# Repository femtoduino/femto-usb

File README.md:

femto-usb
=========

FemtoUSB - Atmel ARM Cortex M0+ (SAMD21), 256KB @ 48MHz, 3V3

This micro controller is designed as a basic starting point for those interested in ARM designs (especially if you are transitioning from 8-bit AVR chips).

We use Atmel's ARM Cortex M0+ offering, the ATSAMD21E18A. The schematic follows the suggested design found in the SAM D21 data sheet.

## Arduino Setup (TLDR)

Arduino compatible when using FemtoUSB (ARM) r1.0.1, with RGB LED.

Just add us to your Arduino IDE. See README https://github.com/femtoio/ArduinoCore-atsamd21e18a/tree/atsamd21e18a_variant

## Why Atmel?
Atmel has some of the best support for the open-source hardware community. They offer proper documentation, excellent chip performance, and a great foundation via the Atmel Software Framework.
Did we mention how easy it is to get started with ARM using ATMEL?

## Key similarities, and differences between 8-bit AVR chips, and newer ARM chips

So, you've been working with Arduino boards for a while now, but want to get into ARM chips right? How difficult can it be?

As it turns out, it's much less so today than it was a short time ago. Thankfully, most micro controllers have a similar set of requirements:

1. Add in some snubbing caps, as per the chip's data sheet.
2. Add in some resistors, as per the chip's data sheet.
3. Add the reset circuit.
4. Add a "power on" LED, making sure to wire up voltage and ground pins correctly.
5. Hook up a USB port, as per the chip's data sheet.
6. Burn a boot loader.

You can of course, add in a reverse current protection circuit, a crystal clock source for chips that don't have an internal one (or if you want a faster clock source), some fancy peripheral additions, etc... but at the most basic design, both 8-bit AVR chips and ARM chips have similar design requirements.

However, here's where we will draw an imaginary line, and now distinguish between 8-bit AVRs and 16/32-bit ARM chips.

When working with ARM chips, you will need a programmer dongle to initially burn a boot loader. 
"Serial Wire Debug" seems to be the most basic form of the [JTAG](http://en.wikipedia.org/wiki/Joint_Test_Action_Group) interface - something provided by all ARM chips. 
This is akin to the "Ardiuno ISP" mode of programming. 
Keep in mind, however, not all chips "talk the same" between the chip and a dongle. Kind of like how two people can have the same interface (vocal chords), but speak different languages. 
Fortunately, it seems Atmel's SAM D21 chips talk "CMSIS" [Cortex Microcontroller Software Interface Standard](http://www.arm.com/products/processors/cortex-m/cortex-microcontroller-software-interface-standard.php), which is a vendor-independent hardware abstraction layer for the Cortex-M processor series.
This is another great reason to use Atmel's line of ARM chips, for what it's worth.

The pins used to provide a JTAG connection vary depending on the ARM chip used, and provide more debugging features when more pins are added.
For the most part, JTAG "Serial Wire Debug" establishes these five (5) connections:

* Ground
* Voltage Reference (Does not supply voltage, you must tie your regulated voltage source to this line when connecting a dongle to a board)
* RESET
* SWCLK (Serial Wire Clock, sometimes overlaid on the "TCK" pin)
* SWDIO (Serial Wire Debug Input/Output, sometimes overlaid on the "TMS" pin)

Your programming dongle should have a data sheet telling you the pin out provided, so you can wire it to your board accordingly.

Another key difference, *and a very important one at that*, is the voltage!

You may be used to 5V logic levels working with Atmel's 8-bit chips... but 5V can be utterly destructive to an ARM chip, as they are meant to work with less power.
The usual voltage range for Atmel's line of ARM chips is somewhere between 1.8V to 3.3V. 
Failure to heed this notice will likely result in the production of a tiny paperweight, instead of a micro controller. 

Ok, I suppose we can move forward. Let's get everything we need to build one.

## Building your own board
The following instructions should help you build your own ARM board. Please follow common workplace and ESD safety practices, and ensure proper ventilation. Solder paste, solder rework, PCB fibers, hot air rework nozzles, soldering irons, and so on, should all be handled with proper safety in mind.
Please observe you local materials safety and disposal laws/guides. We assume no liability whatsoever. Not even. Just no.

### Equipment
As with all ARM chips, you will benefit greatly from having a programmer dongle.
Some vendors lock their chips behind really expensive software tools, and even more expensive programmer dongles ($200+). 
Oh, and have fun trying to get their proprietary stuff working with your open source setup.

Thankfully, Atmel offers their ATMEL-ICE programmer at a reasonable price of [about $85 USD](http://store.atmel.com/PartDetail.aspx?q=p:10500375#tc:description).
I hear you can get them much cheaper without the case, though don't expect it to come with ribbon cables if you go the cheap route.

Please source the following equipment:
* An [ATMEL-ICE programmer](http://www.atmel.com/tools/atatmel-ice.aspx)
* A Windows, Mac OS X, or Linux machine. (Though you may initially require a Windows machine to burn the SAM-BA bootloader using Atmel Studio.)
* Two (2) USB "Micro B" cable. Some cables are less than useless. Try to use ones without a choke if you get any trouble with USB connections.
* Round jumper wires.
* Bread board.
* A reflow station. We use a [Sparkfun Hot-air Rework Station](https://www.sparkfun.com/products/10706)
* A good pair of tweezers. See [Adafruit's offering](http://www.adafruit.com/products/421?gclid=CN-E8eah5MMCFU9efgodj3IAJQ)
* [Helping third hand](http://www.adafruit.com/product/291)
* A multimeter.

Additionally, you will need the following supplies:
* Low temp Lead-free solder paste. We recommend [Pieco's  paste press dispenser bundle with the ChipQuik T5 paste](https://www.tindie.com/products/Pieco/paste-press/) or similar.  
* Some PCBs. You can order them from [OSH Park](https://oshpark.com/shared_projects/F0wPGZvV), or open up the Eagle PCB designs to modify and make your own (see the FemtoUSB_r1.0.0 folder, open up the femtoUSB_r1.0.0_TQFP board and schematic)
* The SMD components. [Thanks Octopart!](https://octopart.com/bom-lookup/UgbhotEt) ...the gerbers and parts lists can also be found within the `FemtoUSB_r1.0.0/femtoUSB_r1.0.0_TQFP/` folder

### Software tools
On windows, you will need
* Atmel Studio (6.2.x as of the time of this writing)

On Mac OS X, and Linux
* [Terry Guo's GNU ARM Embedded Toolchain.](https://launchpad.net/~terry.guo/+archive/ubuntu/gcc-arm-embedded) (Ubuntu user's can add a PPA and have the apt-get package manager install it)
* Legit command line ninja skills.
* Make tools.

For any machine you are on, you will also need the following:

* [Atmel Software Framework (ASF)](http://www.atmel.com/tools/avrsoftwareframework.aspx?tab=overview)
* [Atmel SAM-BA In-system Programmer](http://www.atmel.com/tools/ATMELSAM-BAIN-SYSTEMPROGRAMMER.aspx)
* [Atmel AT07175: SAM-BA Bootloader for SAM D21](http://www.atmel.com/devices/atsamd21e18a.aspx?tab=documents) ...Note, this is what actually gets programmed on to the chip so we can load stuff via USB instead.

### Assembling a board, or three.
For the most part, try not to make a mess of solder paste everywhere. Add just enough to cover the solder pads with a thin layer, and place the correct part according to the femtoUSB_r1.0.0_TQFP_parts.csv spread sheet.
If you don't have the 4-layer or more version of Eagle PCB, you can also look at the femtoUSB_r1.0.0_TQFP.pdf file for schematics and board drawings. See `FemtoUSB_r1.0.0/femtoUSB_r1.0.0_TQFP/`

Once you have everything assembled, make sure your board is secured by the "helping third hand" tool, and remove any nozzle attachments from your reflow station to get the widest air flow. 
Heat up your reflow station to around 200c - 210c or so. The low temperature lead-free solder paste should not require too much heat. Air flow should be kept low (I dial it down to level 4 on my Sparkfun Hot-air Rework station).
Go ahead and adjust the temperature and air flow as you see fit. A constant stream of hot air should reflow stuff within a minute or less.

Be certain to keep the air flow on the USB connection a bit longer than the rest of the board, as the pads underneath the USB connector may take a few seconds longer to heat up.

*Allow your boards to cool down on their own before handling!*

### Testing and programming
Grab you multimeter, switch it to the "open circuit" checking mode (you know, the one that beeps when touch the two leads).
Test between the GND (Ground) pin and all other pins to assert there are no shorts between Ground and the rest of the pins. 
Do the same between voltage and other pins. As a last step, you can also test by steping pegs, (testing between two concurrent pins, moving up by one pin at a time).
This last step is mostly necessary if you have a hard time checking the board for shorts or gaps visually.

Now, it's time to give our board(s) a bootloader!

Wire the following pins together, tying the two "GND" pins from the ATMEL-ICE programmer dongle on to a breadboard, so you can use a single wire from the breadboard GND line to the board's GND pin.
Additionally, you will need to make sure the board's 3V3 (regulated) volatage pin is tied to the programmer dongle's VTG (voltage reference) pin, as the programmer dongle does *not* supply voltage. It merely detects the voltage level with the VREF line.

*DO NOT MIX UP THE "SAM" PORT WITH THE "AVR" PORT, AS THE PINOUT IS DIFFERENT!*

| ATMEL-ICE "SAM" port           | Your Board     |
|--------------------------------|----------------|
| SWDCLK (SAM Pin 4)             | SWDCLK (PA31)  |
| SWDIO (SAM Pin 2)              | SWDIO (PA30)   |
| nRST (SAM Pin 10, labeled "0") | RESET          |
| VTG (SAM Pin 1)                | 3V3 (Regulated)|
| GND (SAM Pin 3, 5)             | GND            |

#### Windows
Open up Atmel Studio on your Windows machine, plug in the USB cable for your board, plug in the USB cable for your programmer dongle.
Your board should power on, the programmer should have both a red LED and a green LED powered on.

If only the red programmer dongle LED turns on, check for loose connections and check for any solder issues on your board. At worse, build another one with a different PCB and try again.
Don't worry about the semi-on blue LED on your board. That's just the SWDCLK line. You can unsolder it if it bugs you. 

Once you have a good board hooked up, and Atmel Studio running, open up the Device Programmer dialog by navigating to the Tools -> Device Programmer menu item.

In the Device Programmer dialog, select "ATMEL-ICE" as the tool, select "ATSAMD21E18A" as the device (double check to be certain you read this right), and select "SWD" as the interface. 
Click the "Apply" button. Set the "SWD Clock" value to anything from 32KHz to 2MHz and click "Set".
2MHz is plenty fast, but if you ever run into issues reading the chip, try going as low as 32KHz.

You should now click the "Read" button under "Device Signature" to see if you get back a hex value. The board's blue LED will go from semi-off, to bright blue.
If you get a message saying your device is unreadable, double check your connections, double check your solder work, and try again.

Assuming you got back a hex value under "Device Signature", congrats! You appear to have a functional board!

Let's now burn the bootloader.

Click the "Memories" section of the Device Programmer dialog. In the "Flash" area, use the file navigator button to browse to the downloaded (and extracted) `Atmel-42366-SAM-BA-Bootloader-for-SAM-D21_ApplicationNote_AT07175/load sam-ba/samd21e18a/` folder, and select `samd21_sam_ba_usbcdc.hex`
Assert the "Erase Flash before programming" and "Verify Flash after programming" checkboxes are checked. Click "Program". After a brief moment, the Device Programmer dialog should come back with:

```
Erasing device... OK
Programming Flash...OK
Verifying Flash...OK
```

Success! You now have a board with the SAM-BA bootloader! If you're on a Windows machine, you may notice Windows will now attempt to install drivers for the new device. The Windows driver install tool should succeed in finding the correct drivers.
You can now see your board on Linux/Mac as well. Simply plug it in via USB, and run the 'lsusb' command from a terminal. You will see an Atmel 'SAM-BA' device listing.

#### GNU/Linux (Ubuntu)

You will need to install Terry Guo's arm-none-eabi-* toolchain, OpenOCD, and the build-essentails package.

To load stuff over USB CDC, you will need either Atmel's SAM-BA utility, or the 'arduino' branch of the BOSSA utility (compiled from source). See https://github.com/femtoio/BOSSA

```
# Thanks to Patryk Jaworski for a wonderful blog article
# http://regalis.com.pl/en/arm-cortex-stm32-gnulinux/
openocd -f /path/to/boardconfig.cfg
```
Then, in a separate terminal:
```
telnet localhost 4444
```
...Run the following within telnet:
```
reset halt
flash write_image erase yourfile.hex
reset run
```

## Next Steps
We are working on getting Arduino integration working, along with other non-Arduino tools to load stuff via USB. Stay tuned!

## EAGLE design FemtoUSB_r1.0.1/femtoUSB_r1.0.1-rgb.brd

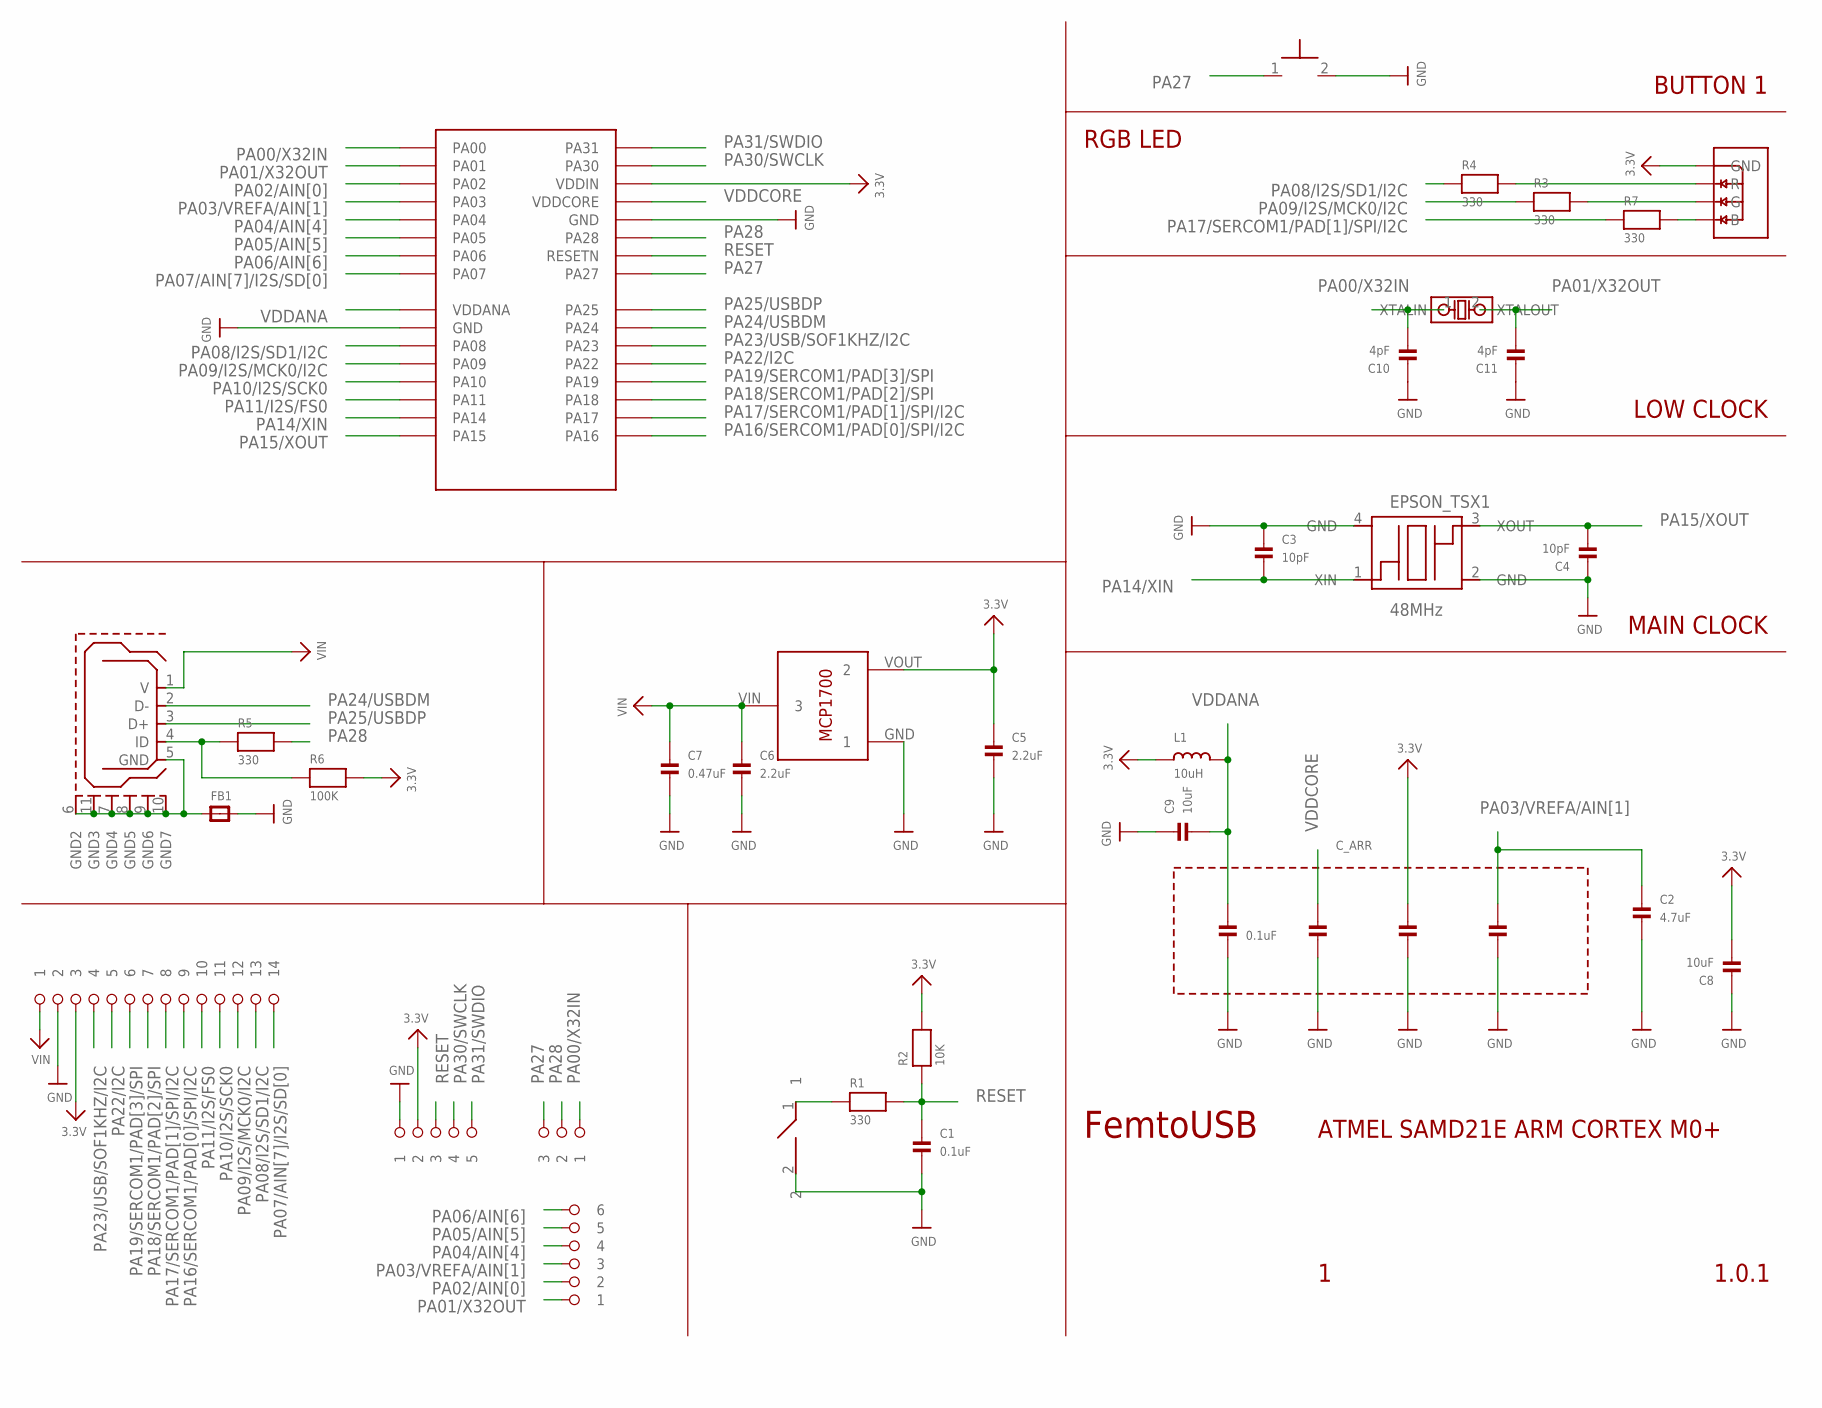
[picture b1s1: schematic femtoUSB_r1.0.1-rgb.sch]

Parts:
BTN_BOOT: TACTILE_SWITCH_NO_GND_NO_BOSS; SIDE_ACT_NO_GND_NO_BOSS
C1: 0.1uF; _0402MP
C2: 4.7uF; _0402MP
C3, C4: 10pF; _0402MP
C5, C6: 2.2uF; _0402MP
C7: 0.47uF; _0402MP
C8, C9: 10uF; _0402MP
C10, C11: 4pF; _0402MP
C_ARR: 0.1uF; CAPACITOR_ARRAY_1206_MONO_1X4
EPSON_TSX1: 48MHz; TSX-3225
FB1: FERRITE_0603MP; _0603MP
IC1: ATSAMD21E18A-MUT; QFN32
L1: 10uH; _0603MP
LDO_VREG: MCP1700T-3302E/TT
MICRO_B_USB: USB_MICROB; USB_MICROB_PACKAGE
OSC32K: ABS06-107-32.768KHZ-T
PIN_1X3: 1X3_ROUND
PIN_1X5: 1X5_ROUND
PIN_1X6: 1X6_ROUND
PIN_1X14: 1X14_ROUND
R1, R3, R4, R5, R7: 330; _0402MP
R2: 10K; _0402MP
R6: 100K; _0402MP
RGBLED: LRTB_R48G
SJ_RESET: SPST_SMD

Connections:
3.3V: C5.1, C8.2, C_ARR.5, IC1.30 (VDDIN), L1.1, LDO_VREG.VOUT (2), PIN_1X5.P$2 (2), PIN_1X14.P$3 (3), R2.2, R6.2, RGBLED.1 (GND)
GND: BTN_BOOT.2, C1.2, C2.2, C3.1, C4.1, C5.2, C6.2, C7.2, C8.1, C9.1, C10.1, C11.1, C_ARR.2, C_ARR.4, C_ARR.6, C_ARR.8, EPSON_TSX1.2 (GND), EPSON_TSX1.4 (GND), FB1.2, IC1.10 (GND), IC1.28 (GND), LDO_VREG.GND (1), PIN_1X5.P$1 (1), PIN_1X14.P$2 (2), SJ_RESET.2
unnamed: MICRO_B_USB.4 (ID), R5.1, R6.1
unnamed: R1.1, SJ_RESET.1
unnamed: FB1.1, MICRO_B_USB.5 (GND), MICRO_B_USB.6 (GND2), MICRO_B_USB.7 (GND4), MICRO_B_USB.8 (GND5), MICRO_B_USB.9 (GND6), MICRO_B_USB.10 (GND7), MICRO_B_USB.11 (GND3)
PA00/X32IN: C10.2, IC1.1 (PA00), OSC32K.1 (XTALIN), PIN_1X3.P$1 (1)
PA01/X32OUT: C11.2, IC1.2 (PA01), OSC32K.2 (XTALOUT), PIN_1X6.P$1 (1)
PA02/AIN[0]: IC1.3 (PA02), PIN_1X6.P$2 (2)
PA03/VREFA/AIN[1]: C2.1, C_ARR.7, IC1.4 (PA03), PIN_1X6.P$3 (3)
PA04/AIN[4]: IC1.5 (PA04), PIN_1X6.P$4 (4)
PA05/AIN[5]: IC1.6 (PA05), PIN_1X6.P$5 (5)
PA06/AIN[6]: IC1.7 (PA06), PIN_1X6.P$6 (6)
PA07/AIN[7]/I2S/SD[0]: IC1.8 (PA07), PIN_1X14.P$14 (14)
PA08/I2S/SD1/I2C: IC1.11 (PA08), PIN_1X14.P$13 (13), R4.1
PA08_R: R4.2, RGBLED.2 (R)
PA09/I2S/MCK0/I2C: IC1.12 (PA09), PIN_1X14.P$12 (12), R3.1
PA09_G: R3.2, RGBLED.3 (G)
PA10/I2S/SCK0: IC1.13 (PA10), PIN_1X14.P$11 (11)
PA11/I2S/FS0: IC1.14 (PA11), PIN_1X14.P$10 (10)
PA14/XIN: C3.2, EPSON_TSX1.1 (XIN), IC1.15 (PA14)
PA15/XOUT: C4.2, EPSON_TSX1.3 (XOUT), IC1.16 (PA15)
PA16/SERCOM1/PAD[0]/SPI/I2C: IC1.17 (PA16), PIN_1X14.P$9 (9)
PA17/SERCOM1/PAD[1]/SPI/I2C: IC1.18 (PA17), PIN_1X14.P$8 (8), R7.1
PA17_B: R7.2, RGBLED.4 (B)
PA18/SERCOM1/PAD[2]/SPI: IC1.19 (PA18), PIN_1X14.P$7 (7)
PA19/SERCOM1/PAD[3]/SPI: IC1.20 (PA19), PIN_1X14.P$6 (6)
PA22/I2C: IC1.21 (PA22), PIN_1X14.P$5 (5)
PA23/USB/SOF1KHZ/I2C: IC1.22 (PA23), PIN_1X14.P$4 (4)
PA24/USBDM: IC1.23 (PA24), MICRO_B_USB.2 (D-)
PA25/USBDP: IC1.24 (PA25), MICRO_B_USB.3 (D+)
PA27: BTN_BOOT.1, IC1.25 (PA27), PIN_1X3.P$3 (3)
PA28: IC1.27 (PA28), PIN_1X3.P$2 (2), R5.2
PA30/SWCLK: IC1.31 (PA30), PIN_1X5.P$4 (4)
PA31/SWDIO: IC1.32 (PA31), PIN_1X5.P$5 (5)
RESET: C1.1, IC1.26 (RESETN), PIN_1X5.P$3 (3), R1.2, R2.1
VDDANA: C9.2, C_ARR.1, IC1.9 (VDDANA), L1.2
VDDCORE: C_ARR.3, IC1.29 (VDDCORE)
VIN: C6.1, C7.1, LDO_VREG.VIN (3), MICRO_B_USB.1 (V), PIN_1X14.P$1 (1)

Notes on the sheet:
FemtoUSB
1.0.1
ATMEL SAMD21E ARM CORTEX M0+
MAIN CLOCK
LOW CLOCK
RGB LED
BUTTON 1

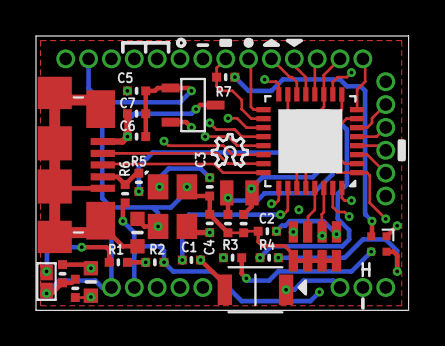
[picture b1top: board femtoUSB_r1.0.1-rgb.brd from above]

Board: 4 copper layers, 20.7 x 15.2 mm, 34 parts (0 on the bottom side), 38 nets.

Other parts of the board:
U$35: OSHW_6X70_NOTEXT

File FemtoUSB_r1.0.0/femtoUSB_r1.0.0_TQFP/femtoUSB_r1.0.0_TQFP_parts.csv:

"Part";"Value";"Device";"Package";"Description";"DIGIKEY_PART"
"BTN";"OMRON B3U-300P(M)";"TACTILE_SWITCH_NO_GND_NO_BOSS";"SIDE_ACT_NO_GND_NO_BOSS";;
"C1";"0.1uF";"CAP_CERAMIC_0402MP";"_0402MP";"Ceramic Capacitors";
"C2";"4.7uF";"CAP_CERAMIC_0402MP";"_0402MP";"Ceramic Capacitors";
"C3";"9pF";"CAP_CERAMIC_0402MP";"_0402MP";"Ceramic Capacitors";
"C4";"9pF";"CAP_CERAMIC_0402MP";"_0402MP";"Ceramic Capacitors";
"C5";"2.2uF";"CAP_CERAMIC_0402MP";"_0402MP";"Ceramic Capacitors";
"C6";"2.2uF";"CAP_CERAMIC_0402MP";"_0402MP";"Ceramic Capacitors";
"C7";"0.47uF";"CAP_CERAMIC_0402MP";"_0402MP";"Ceramic Capacitors";
"C_ARR1";"0.1uF";"KEMET_CERAMIC_CAPACITOR_ARRAY_1X4";"CAPACITOR_ARRAY_1206_MONO_1X4";;"399-8243-1-ND"
"EPSON_TSX1";"32MHz";"TSX-3225";"TSX-3225";;"TSX-3225 32.0000MF15X-B-ND"
"FB1";;"FERRITE_0603MP";"_0603MP";"Ferrite Bead";
"IC1";"ATSAMD21E18A-AU";"ATSAMD21E18A-AU";"32-TQFP";;
"LDO_VREG";"MCP1700T-3302E/TT";"MCP1700T-3302E/TT";"MCP1700T-3302E/TT";;
"LED1";"RED";"LED0603_NOOUTLINE";"CHIPLED_0603_NOOUTLINE";"LED";
"LED2";"GREEN";"LED0603_NOOUTLINE";"CHIPLED_0603_NOOUTLINE";"LED";
"MICRO_B_USB";"USB_MICROB";"USB_MICROB";"USB_MICROB_PACKAGE";"This is the hirose ZX62-B-5PA(11) MICRO-USB B Type female connection.";
"R1";"330";"RESISTOR_0402MP";"_0402MP";"Resistors";
"R2";"10K";"RESISTOR_0402MP";"_0402MP";"Resistors";
"R3";"330";"RESISTOR_0402MP";"_0402MP";"Resistors";
"R4";"330";"RESISTOR_0402MP";"_0402MP";"Resistors";
"U$6";"1X14_ROUND";"1X14_ROUND";"1X14_ROUND";;
"U$7";"1X3_ROUND";"1X3_ROUND";"1X3_ROUND";;
"U$9";"1X5_ROUND";"1X5_ROUND";"1X5_ROUND";;
"U$12";"1X6_ROUND";"1X6_ROUND";"1X6_ROUND";;

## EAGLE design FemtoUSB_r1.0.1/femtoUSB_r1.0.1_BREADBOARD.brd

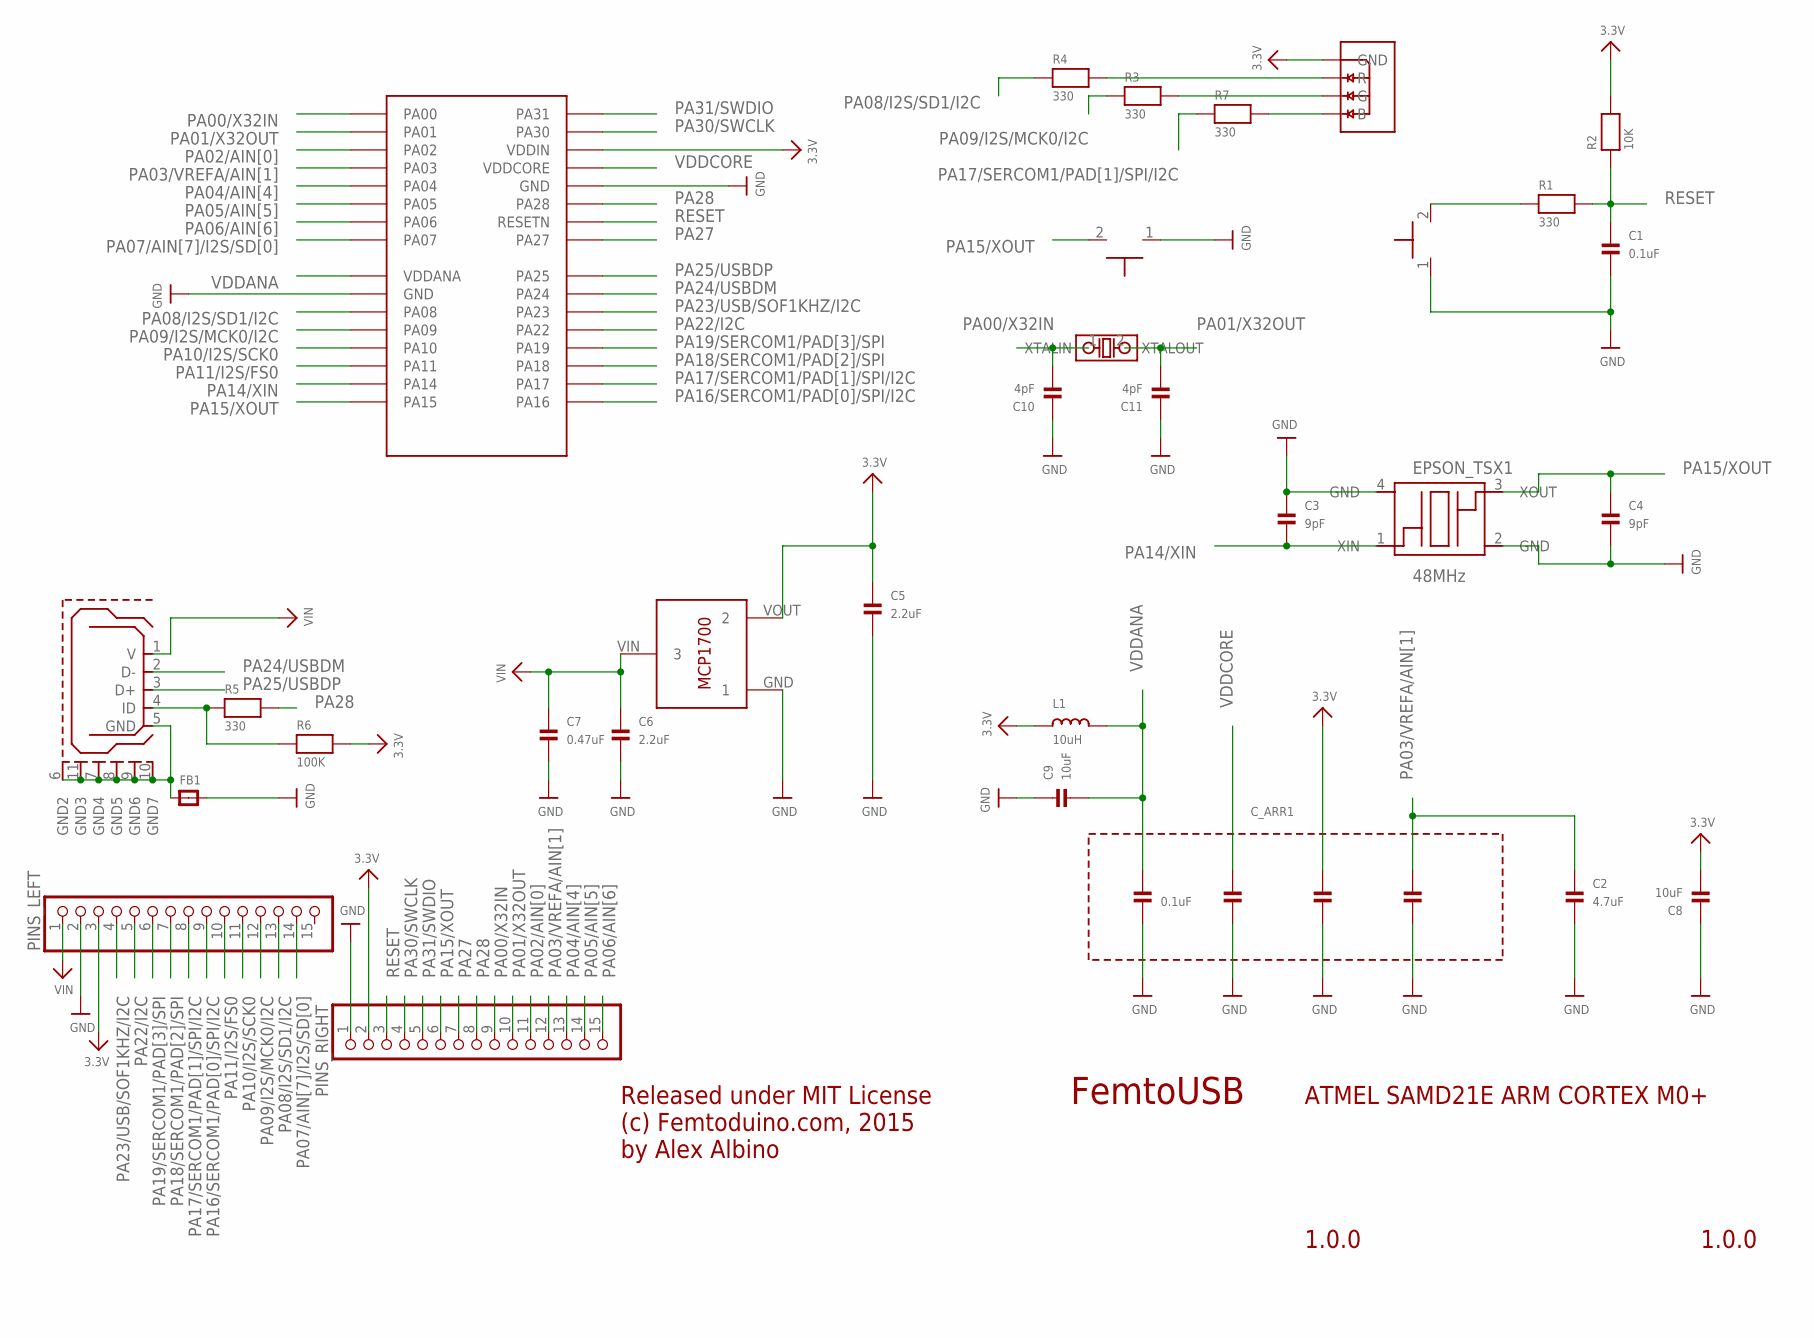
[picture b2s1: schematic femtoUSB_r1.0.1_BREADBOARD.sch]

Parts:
BOOT_BTN, BOOT_BTN1: TACTILE_SWITCH_NO_GND_NO_BOSS; SIDE_ACT_NO_GND_NO_BOSS
C1: 0.1uF; _0402MP; DIGIKEY_PART 445-4958-1-ND
C2: 4.7uF; _0402MP
C3, C4: 9pF; _0402MP
C5, C6: 2.2uF; _0402MP
C7: 0.47uF; _0402MP
C8, C9: 10uF; _0402MP
C10, C11: 4pF; _0402MP
C_ARR1: 0.1uF; CAPACITOR_ARRAY_1206_MONO_1X4
EPSON_TSX1: 48MHz; TSX-3225; DIGIKEY_PART TSX-3225 32.0000MF15X-B-ND
FB1: FERRITE_0603MP; _0603MP
IC1: ATSAMD21E18A-MUT; QFN32; DIGIKEY_PART ATSAMD21E18A-AU-ND
L1: 10uH; _0603MP
LDO_VREG: MCP1700T-3302E/TT
MICRO_B_USB: USB_MICROB; USB_MICROB_PACKAGE
PINS_LEFT: HEADER-1X15; 1X15_ROUND_70
PINS_RIGHT: HEADER-1X15; 1X15_ROUND_70
R1: 330; _0402MP; DIGIKEY_PART 541-330JCT-ND
R2: 10K; _0402MP
R3, R4, R5, R7: 330; _0402MP
R6: 100K; _0402MP
RGBLED: LRTB_R48G
U$40: ABS06-107-32.768KHZ-T

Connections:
3.3V: C5.1, C8.2, C_ARR1.5, IC1.30 (VDDIN), L1.1, LDO_VREG.VOUT (2), PINS_LEFT.3, PINS_RIGHT.2, R2.2, R6.2, RGBLED.1 (GND)
GND: BOOT_BTN.1, BOOT_BTN1.1, C1.2, C2.2, C3.1, C4.2, C5.2, C6.2, C7.2, C8.1, C9.1, C10.1, C11.1, C_ARR1.2, C_ARR1.4, C_ARR1.6, C_ARR1.8, EPSON_TSX1.2 (GND), EPSON_TSX1.4 (GND), FB1.2, IC1.10 (GND), IC1.28 (GND), LDO_VREG.GND (1), PINS_LEFT.2, PINS_RIGHT.1
GND_RAW: FB1.1, MICRO_B_USB.5 (GND), MICRO_B_USB.6 (GND2), MICRO_B_USB.7 (GND4), MICRO_B_USB.8 (GND5), MICRO_B_USB.9 (GND6), MICRO_B_USB.10 (GND7), MICRO_B_USB.11 (GND3)
unnamed: MICRO_B_USB.4 (ID), R5.1, R6.1
unnamed: BOOT_BTN1.2, R1.1
PA00/X32IN: C10.2, IC1.1 (PA00), PINS_RIGHT.9, U$40.1 (XTALIN)
PA01/X32OUT: C11.2, IC1.2 (PA01), PINS_RIGHT.10, U$40.2 (XTALOUT)
PA02/AIN[0]: IC1.3 (PA02), PINS_RIGHT.11
PA03/VREFA/AIN[1]: C2.1, C_ARR1.7, IC1.4 (PA03), PINS_RIGHT.12
PA04/AIN[4]: IC1.5 (PA04), PINS_RIGHT.13
PA05/AIN[5]: IC1.6 (PA05), PINS_RIGHT.14
PA06/AIN[6]: IC1.7 (PA06), PINS_RIGHT.15
PA07/AIN[7]/I2S/SD[0]: IC1.8 (PA07), PINS_LEFT.14
PA08/I2S/SD1/I2C: IC1.11 (PA08), PINS_LEFT.13, R4.1
PA08_R: R4.2, RGBLED.2 (R)
PA09/I2S/MCK0/I2C: IC1.12 (PA09), PINS_LEFT.12, R3.1
PA09_G: R3.2, RGBLED.3 (G)
PA10/I2S/SCK0: IC1.13 (PA10), PINS_LEFT.11
PA11/I2S/FS0: IC1.14 (PA11), PINS_LEFT.10
PA14/XIN: C3.2, EPSON_TSX1.1 (XIN), IC1.15 (PA14)
PA15/XOUT: BOOT_BTN.2, C4.1, EPSON_TSX1.3 (XOUT), IC1.16 (PA15), PINS_RIGHT.6
PA16/SERCOM1/PAD[0]/SPI/I2C: IC1.17 (PA16), PINS_LEFT.9
PA17/SERCOM1/PAD[1]/SPI/I2C: IC1.18 (PA17), PINS_LEFT.8, R7.1
PA17_B: R7.2, RGBLED.4 (B)
PA18/SERCOM1/PAD[2]/SPI: IC1.19 (PA18), PINS_LEFT.7
PA19/SERCOM1/PAD[3]/SPI: IC1.20 (PA19), PINS_LEFT.6
PA22/I2C: IC1.21 (PA22), PINS_LEFT.5
PA23/USB/SOF1KHZ/I2C: IC1.22 (PA23), PINS_LEFT.4
PA24/USBDM: IC1.23 (PA24), MICRO_B_USB.2 (D-)
PA25/USBDP: IC1.24 (PA25), MICRO_B_USB.3 (D+)
PA27: IC1.25 (PA27), PINS_RIGHT.7
PA28: IC1.27 (PA28), PINS_RIGHT.8, R5.2
PA30/SWCLK: IC1.31 (PA30), PINS_RIGHT.4
PA31/SWDIO: IC1.32 (PA31), PINS_RIGHT.5
RESET: C1.1, IC1.26 (RESETN), PINS_RIGHT.3, R1.2, R2.1
VDDANA: C9.2, C_ARR1.1, IC1.9 (VDDANA), L1.2
VDDCORE: C_ARR1.3, IC1.29 (VDDCORE)
VIN: C6.1, C7.1, LDO_VREG.VIN (3), MICRO_B_USB.1 (V), PINS_LEFT.1

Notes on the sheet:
FemtoUSB
1.0.0
ATMEL SAMD21E ARM CORTEX M0+
Released under MIT License (c) Femtoduino.com, 2015 by Alex Albino

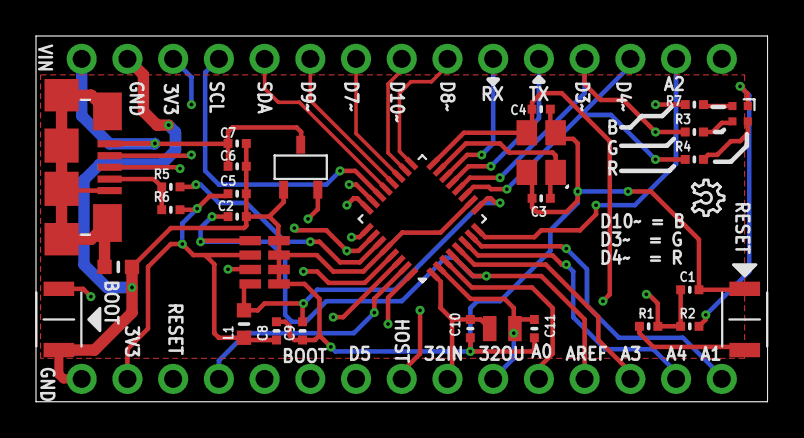
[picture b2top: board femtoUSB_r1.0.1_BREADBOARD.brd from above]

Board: 4 copper layers, 40.6 x 20.3 mm, 32 parts (0 on the bottom side), 38 nets.

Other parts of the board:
OSH_LOGO: OSHW_6X70_NOTEXT

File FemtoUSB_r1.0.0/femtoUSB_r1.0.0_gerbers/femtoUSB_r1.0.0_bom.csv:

"Qty";"Value";"Device";"Package";"Parts";"Description";"DIGIKEY_PART";
"1";"";"FERRITE_0603MP";"_0603MP";"FB1";"Ferrite Bead";"";
"1";"0.1uF";"CAP_CERAMIC_0402MP";"_0402MP";"C1";"Ceramic Capacitors";"";
"1";"0.1uF";"KEMET_CERAMIC_CAPACITOR_ARRAY_1X4";"CAPACITOR_ARRAY_1206_MONO_1X4";"C_ARR1";"";"";
"1";"0.47uF";"CAP_CERAMIC_0402MP";"_0402MP";"C7";"Ceramic Capacitors";"";
"1";"10K";"RESISTOR_0402MP";"_0402MP";"R2";"Resistors";"";
"1";"1X14_ROUND";"1X14_ROUND";"1X14_ROUND";"U$6";"";"";
"1";"1X3_ROUND";"1X3_ROUND";"1X3_ROUND";"U$7";"";"";
"1";"1X5_ROUND";"1X5_ROUND";"1X5_ROUND";"U$9";"";"";
"1";"1X6_ROUND";"1X6_ROUND";"1X6_ROUND";"U$12";"";"";
"2";"2.2uF";"CAP_CERAMIC_0402MP";"_0402MP";"C5, C6";"Ceramic Capacitors";"";
"1";"32MHz";"TSX-3225";"TSX-3225";"EPSON_TSX1";"";"TSX-3225 32.0000MF15X-B-ND";
"3";"330";"RESISTOR_0402MP";"_0402MP";"R1, R3, R4";"Resistors";"";
"1";"4.7uF";"CAP_CERAMIC_0402MP";"_0402MP";"C2";"Ceramic Capacitors";"";
"2";"9pF";"CAP_CERAMIC_0402MP";"_0402MP";"C3, C4";"Ceramic Capacitors";"";
"1";"ATSAMD21E18A-MUT";"ATSAMD21E18A-MUT";"QFN32";"IC1";"This is the ATMEL SAMD21E QFN-32. ATSAMD21E18A";"";
"1";"GREEN";"LED0603_NOOUTLINE";"CHIPLED_0603_NOOUTLINE";"LED2";"LED";"";
"1";"LM3480";"LM3480";"LM3480";"LDO_VREG";"";"";
"1";"OMRON B3U-300P(M)";"TACTILE_SWITCH_NO_GND_NO_BOSS";"SIDE_ACT_NO_GND_NO_BOSS";"BTN";"";"";
"1";"RED";"LED0603_NOOUTLINE";"CHIPLED_0603_NOOUTLINE";"LED1";"LED";"";
"1";"USB_MICROB";"USB_MICROB";"USB_MICROB_PACKAGE";"MICRO_B_USB";"This is the hirose ZX62-B-5PA(11) MICRO-USB B Type female connection.";"";

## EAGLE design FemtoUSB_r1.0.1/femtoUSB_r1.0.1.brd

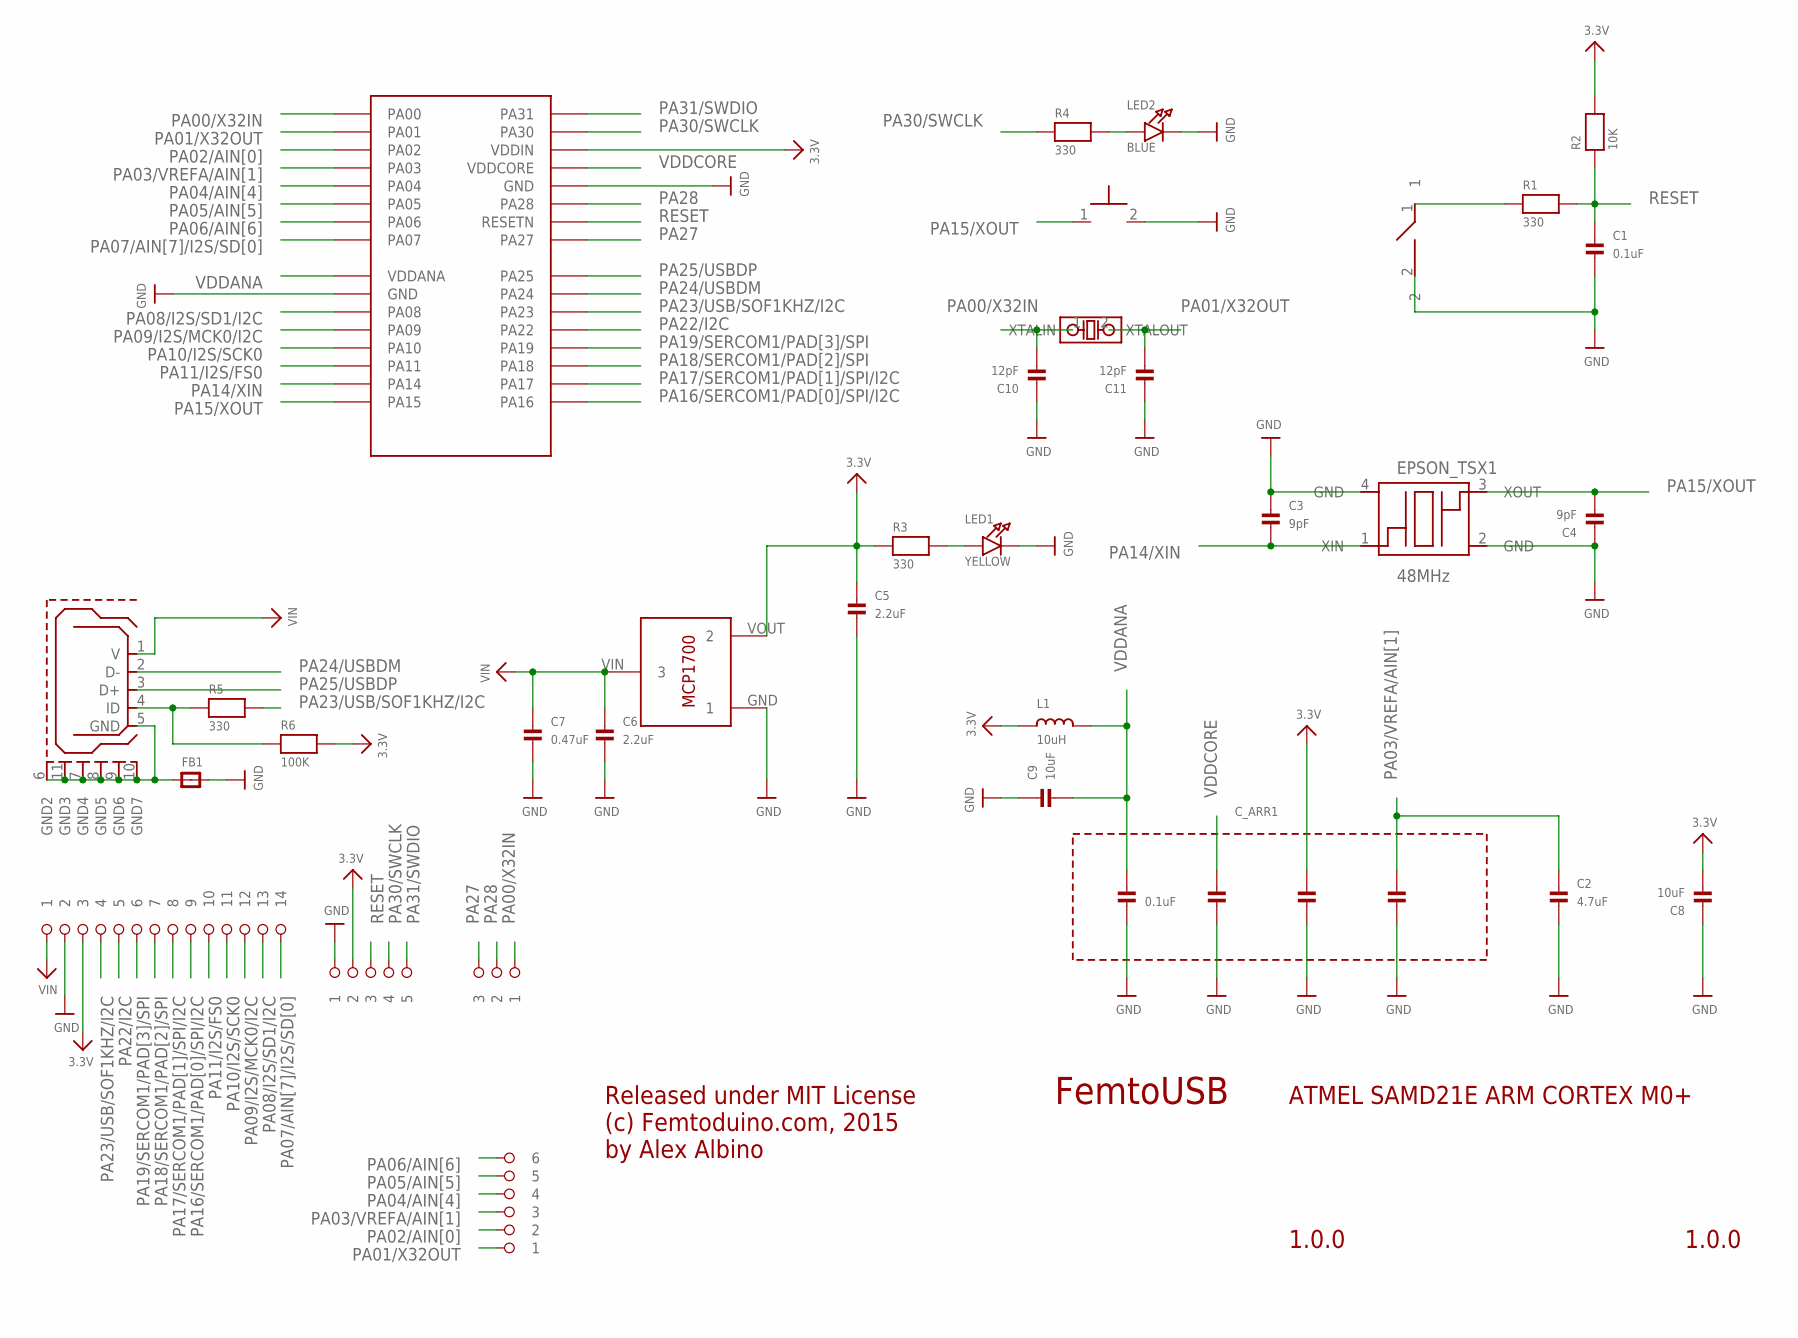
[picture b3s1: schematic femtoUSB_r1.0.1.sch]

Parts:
BTN: OMRON B3U-300P(M); SPST_SMD
C1: 0.1uF; _0402MP
C2: 4.7uF; _0402MP
C3, C4: 9pF; _0402MP
C5, C6: 2.2uF; _0402MP
C7: 0.47uF; _0402MP
C8, C9: 10uF; _0402MP
C10, C11: 12pF; _0402MP
C_ARR1: 0.1uF; CAPACITOR_ARRAY_1206_MONO_1X4
EPSON_TSX1: 48MHz; TSX-3225; DIGIKEY_PART TSX-3225 32.0000MF15X-B-ND
FB1: FERRITE_0603MP; _0603MP
IC1: ATSAMD21E18A-MUT; QFN32
L1: 10uH; _0603MP
LDO_VREG: MCP1700T-3302E/TT
LED1: YELLOW; CHIPLED_0603_NOOUTLINE
LED2: BLUE; CHIPLED_0603_NOOUTLINE
MICRO_B_USB: USB_MICROB; USB_MICROB_PACKAGE
R1, R3, R4, R5: 330; _0402MP
R2: 10K; _0402MP
R6: 100K; _0402MP
U$6: 1X14_ROUND
U$7: 1X3_ROUND
U$9: 1X5_ROUND
U$12: 1X6_ROUND
U$40: ABS06-107-32.768KHZ-T
U$43: TACTILE_SWITCH_NO_GND_NO_BOSS; SIDE_ACT_NO_GND_NO_BOSS

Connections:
3.3V: C5.1, C8.2, C_ARR1.5, IC1.30 (VDDIN), L1.1, LDO_VREG.VOUT (2), R2.2, R3.1, R6.2, U$6.P$3 (3), U$9.P$2 (2)
GND: BTN.2, C1.2, C2.2, C3.1, C4.1, C5.2, C6.2, C7.2, C8.1, C9.1, C10.1, C11.1, C_ARR1.2, C_ARR1.4, C_ARR1.6, C_ARR1.8, EPSON_TSX1.2 (GND), EPSON_TSX1.4 (GND), FB1.2, IC1.10 (GND), IC1.28 (GND), LDO_VREG.GND (1), LED1.C, LED2.C, U$6.P$2 (2), U$9.P$1 (1), U$43.2
unnamed: LED1.A, R3.2
unnamed: MICRO_B_USB.4 (ID), R5.1, R6.1
unnamed: LED2.A, R4.2
unnamed: BTN.1, R1.1
unnamed: FB1.1, MICRO_B_USB.5 (GND), MICRO_B_USB.6 (GND2), MICRO_B_USB.7 (GND4), MICRO_B_USB.8 (GND5), MICRO_B_USB.9 (GND6), MICRO_B_USB.10 (GND7), MICRO_B_USB.11 (GND3)
PA00/X32IN: C10.2, IC1.1 (PA00), U$7.P$1 (1), U$40.1 (XTALIN)
PA01/X32OUT: C11.2, IC1.2 (PA01), U$12.P$1 (1), U$40.2 (XTALOUT)
PA02/AIN[0]: IC1.3 (PA02), U$12.P$2 (2)
PA03/VREFA/AIN[1]: C2.1, C_ARR1.7, IC1.4 (PA03), U$12.P$3 (3)
PA04/AIN[4]: IC1.5 (PA04), U$12.P$4 (4)
PA05/AIN[5]: IC1.6 (PA05), U$12.P$5 (5)
PA06/AIN[6]: IC1.7 (PA06), U$12.P$6 (6)
PA07/AIN[7]/I2S/SD[0]: IC1.8 (PA07), U$6.P$14 (14)
PA08/I2S/SD1/I2C: IC1.11 (PA08), U$6.P$13 (13)
PA09/I2S/MCK0/I2C: IC1.12 (PA09), U$6.P$12 (12)
PA10/I2S/SCK0: IC1.13 (PA10), U$6.P$11 (11)
PA11/I2S/FS0: IC1.14 (PA11), U$6.P$10 (10)
PA14/XIN: C3.2, EPSON_TSX1.1 (XIN), IC1.15 (PA14)
PA15/XOUT: C4.2, EPSON_TSX1.3 (XOUT), IC1.16 (PA15), U$43.1
PA16/SERCOM1/PAD[0]/SPI/I2C: IC1.17 (PA16), U$6.P$9 (9)
PA17/SERCOM1/PAD[1]/SPI/I2C: IC1.18 (PA17), U$6.P$8 (8)
PA18/SERCOM1/PAD[2]/SPI: IC1.19 (PA18), U$6.P$7 (7)
PA19/SERCOM1/PAD[3]/SPI: IC1.20 (PA19), U$6.P$6 (6)
PA22/I2C: IC1.21 (PA22), U$6.P$5 (5)
PA23/USB/SOF1KHZ/I2C: IC1.22 (PA23), R5.2, U$6.P$4 (4)
PA24/USBDM: IC1.23 (PA24), MICRO_B_USB.2 (D-)
PA25/USBDP: IC1.24 (PA25), MICRO_B_USB.3 (D+)
PA27: IC1.25 (PA27), U$7.P$3 (3)
PA28: IC1.27 (PA28), U$7.P$2 (2)
PA30/SWCLK: IC1.31 (PA30), R4.1, U$9.P$4 (4)
PA31/SWDIO: IC1.32 (PA31), U$9.P$5 (5)
RESET: C1.1, IC1.26 (RESETN), R1.2, R2.1, U$9.P$3 (3)
VDDANA: C9.2, C_ARR1.1, IC1.9 (VDDANA), L1.2
VDDCORE: C_ARR1.3, IC1.29 (VDDCORE)
VIN: C6.1, C7.1, LDO_VREG.VIN (3), MICRO_B_USB.1 (V), U$6.P$1 (1)

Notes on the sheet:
FemtoUSB
1.0.0
ATMEL SAMD21E ARM CORTEX M0+
Released under MIT License (c) Femtoduino.com, 2015 by Alex Albino

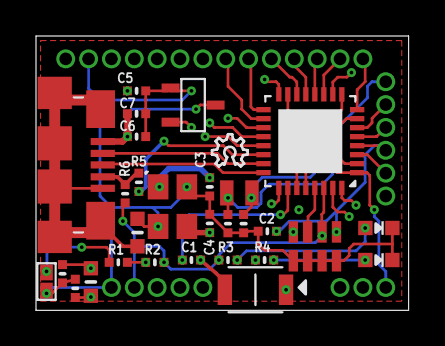
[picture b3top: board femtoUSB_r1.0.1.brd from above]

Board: 4 copper layers, 20.7 x 15.2 mm, 34 parts (0 on the bottom side), 37 nets.

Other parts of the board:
U$35: OSHW_6X70_NOTEXT

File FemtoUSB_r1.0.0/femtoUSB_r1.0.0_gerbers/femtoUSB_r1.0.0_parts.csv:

"Part";"Value";"Device";"Package";"Description"
"C1";"0.1uF";"CAP_CERAMIC_0402MP";"_0402MP";"Ceramic Capacitors"
"C2";"4.7uF";"CAP_CERAMIC_0402MP";"_0402MP";"Ceramic Capacitors"
"C3";"10pF";"CAP_CERAMIC_0402MP";"_0402MP";"Ceramic Capacitors"
"C4";"10pF";"CAP_CERAMIC_0402MP";"_0402MP";"Ceramic Capacitors"
"C5";"2.2uF";"CAP_CERAMIC_0402MP";"_0402MP";"Ceramic Capacitors"
"C6";"2.2uF";"CAP_CERAMIC_0402MP";"_0402MP";"Ceramic Capacitors"
"C7";"0.47uF";"CAP_CERAMIC_0402MP";"_0402MP";"Ceramic Capacitors"
"C8";"10uF";"CAP_CERAMIC_0402MP";"_0402MP";"Ceramic Capacitors"
"C9";"10uF";"CAP_CERAMIC_0402MP";"_0402MP";"Ceramic Capacitors"
"C_ARR1";"0.1uF";"KEMET_CERAMIC_CAPACITOR_ARRAY_1X4";"CAPACITOR_ARRAY_1206_MONO_1X4";
"EPSON_TSX1";"48MHz";"TSX-3225";"TSX-3225";"FA-238 48.0000MB-K3"
"FB1";;"FERRITE_0603MP";"_0603MP";"Ferrite Bead"
"IC1";"ATSAMD21E18A-MUT";"ATSAMD21E18A-MUT";"QFN32";"This is the ATMEL SAMD21E QFN-32. ATSAMD21E18A"
"L1";"10uH";"INDUCTOR_0603MP";"_0603MP";"Fixed Inductor."
"LDO_VREG";"LM3480";"LM3480";"LM3480";
"LED1";"RED";"LED0603_NOOUTLINE";"CHIPLED_0603_NOOUTLINE";"LED"
"LED2";"GREEN";"LED0603_NOOUTLINE";"CHIPLED_0603_NOOUTLINE";"LED"
"MICRO_B_USB";"USB_MICROB";"USB_MICROB";"USB_MICROB_PACKAGE";"This is the hirose ZX62-B-5PA(11) MICRO-USB B Type female connection."
"R1";"330";"RESISTOR_0402MP";"_0402MP";"Resistors"
"R2";"10K";"RESISTOR_0402MP";"_0402MP";"Resistors"
"R3";"330";"RESISTOR_0402MP";"_0402MP";"Resistors"
"R4";"330";"RESISTOR_0402MP";"_0402MP";"Resistors"
"U$6";"1X14_ROUND";"1X14_ROUND";"1X14_ROUND";"1.27mm Pitch"
"U$7";"1X3_ROUND";"1X3_ROUND";"1X3_ROUND";"1.27mm Pitch"
"U$9";"1X5_ROUND";"1X5_ROUND";"1X5_ROUND";"1.27mm Pitch"
"U$12";"1X6_ROUND";"1X6_ROUND";"1X6_ROUND";"1.27mm Pitch"

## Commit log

2015-01-06 Initial release 1.0.0
2015-01-06 Adding license to root of project
2015-01-06 Adding TQFP chip variety
2015-01-22 Corrected the Make and model of the LDO Voltage Regulator. Board now powers on.
2015-02-01 Corrected the snubbing circuits by adding the missing 10uH inductor, and two missing 10uF capacitors. Also corrected the connection from VDDIN pin to 3V3
2015-02-15 Updating README to include basic welcome for makers transitioning from AVR to ARM, along with setup and build instructions
2015-02-15 Minor formatting issues updated
2015-02-15 Minor formatting updates
2015-02-17 Updating the QFN (no leads) chip version of the board - adding in missing 10uF caps and 10uH inductor
2015-02-17 Adding in PDFs, removing Notice labels, as boards appear to work now
2015-02-24 Adding in Atmel SAM-BA bootloader download and chip datasheet, for everyone's convenience.
2015-02-24 adding in fuse values from Atmel Studio
2015-03-20 Updating r1.x version of FemtoUSB (QFN and QFP chip version). Pin PA15 and GND pads now available to start board up in bootloader mode (SAM-BA)
2015-03-28 Releasing the bread-board friendly variant of the FemtoUSB ARM board
2015-03-28 Updating readme
2015-04-03 Added Gitter badge
2015-04-16 Adding OpenOCD config file, and notes about boot loading using non-windows machines
2015-04-28 Adding in bare chip config for ATSAMR21E18A, which is just a SAM D21 + AT86RF233 integrated, and hooked up internally to certain GPIO pins
2015-06-18 Updating gerbers and BoM/Partslist of QFN version
2016-02-08 Updating FemtoUSB to r1.0.1 (EXPERIMENTAL)
2016-02-12 Our first Arduino example for the Atme ATSAMD21E18 based FemtoUSB
2016-02-14 Adding femtoUSB_r1.0.1-rgb design. Uses RGB LED instead of standard SMD LEDs
2016-02-16 Updating breadboard version. Adjusting USB ID pin connection back to PA28 on both FemtoUSB, and FemtoUSB breadboard layout
2016-02-16 Updating FemtoUSB r1.0.1 breadboard version
2016-02-16 Updating FemtoUSB Breadboard desing. Using QFN only
2016-02-16 Removing lock files, shouldnt have those committed.
2016-03-07 Updating FemtoUSB r1.0.1 w/ RGB. Silkscreen updated to reflect Arduino pin assignments
2016-03-07 Updating cap value for 32.768KHz crystal to correct value, adding in example sketches
2016-03-07 Updating Bill of Materials, and component attributes to include mfr ID. Button is now used by PA27 instead of PA15 (boot), since Arduino core doesn't need the boot pin to upload subsequent sketches
2016-03-07 Updating PNG of r1.0.1 w/ RGB
2016-03-16 Update to setup info for RGB_SerialControl sketch
2016-03-17 Updating RGB_LED example sketch
2016-03-25 Caps for 48MHz updated from 9pF to 10pF. Updated to correct manufacturor ID for too. Minor fix to skewed polygon - was supposed to be rectangular.

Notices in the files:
parts and their libraries:
microbuilder: This work is placed in the public domain, and may be freely used for commercial and non-commercial work with the following conditions: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
